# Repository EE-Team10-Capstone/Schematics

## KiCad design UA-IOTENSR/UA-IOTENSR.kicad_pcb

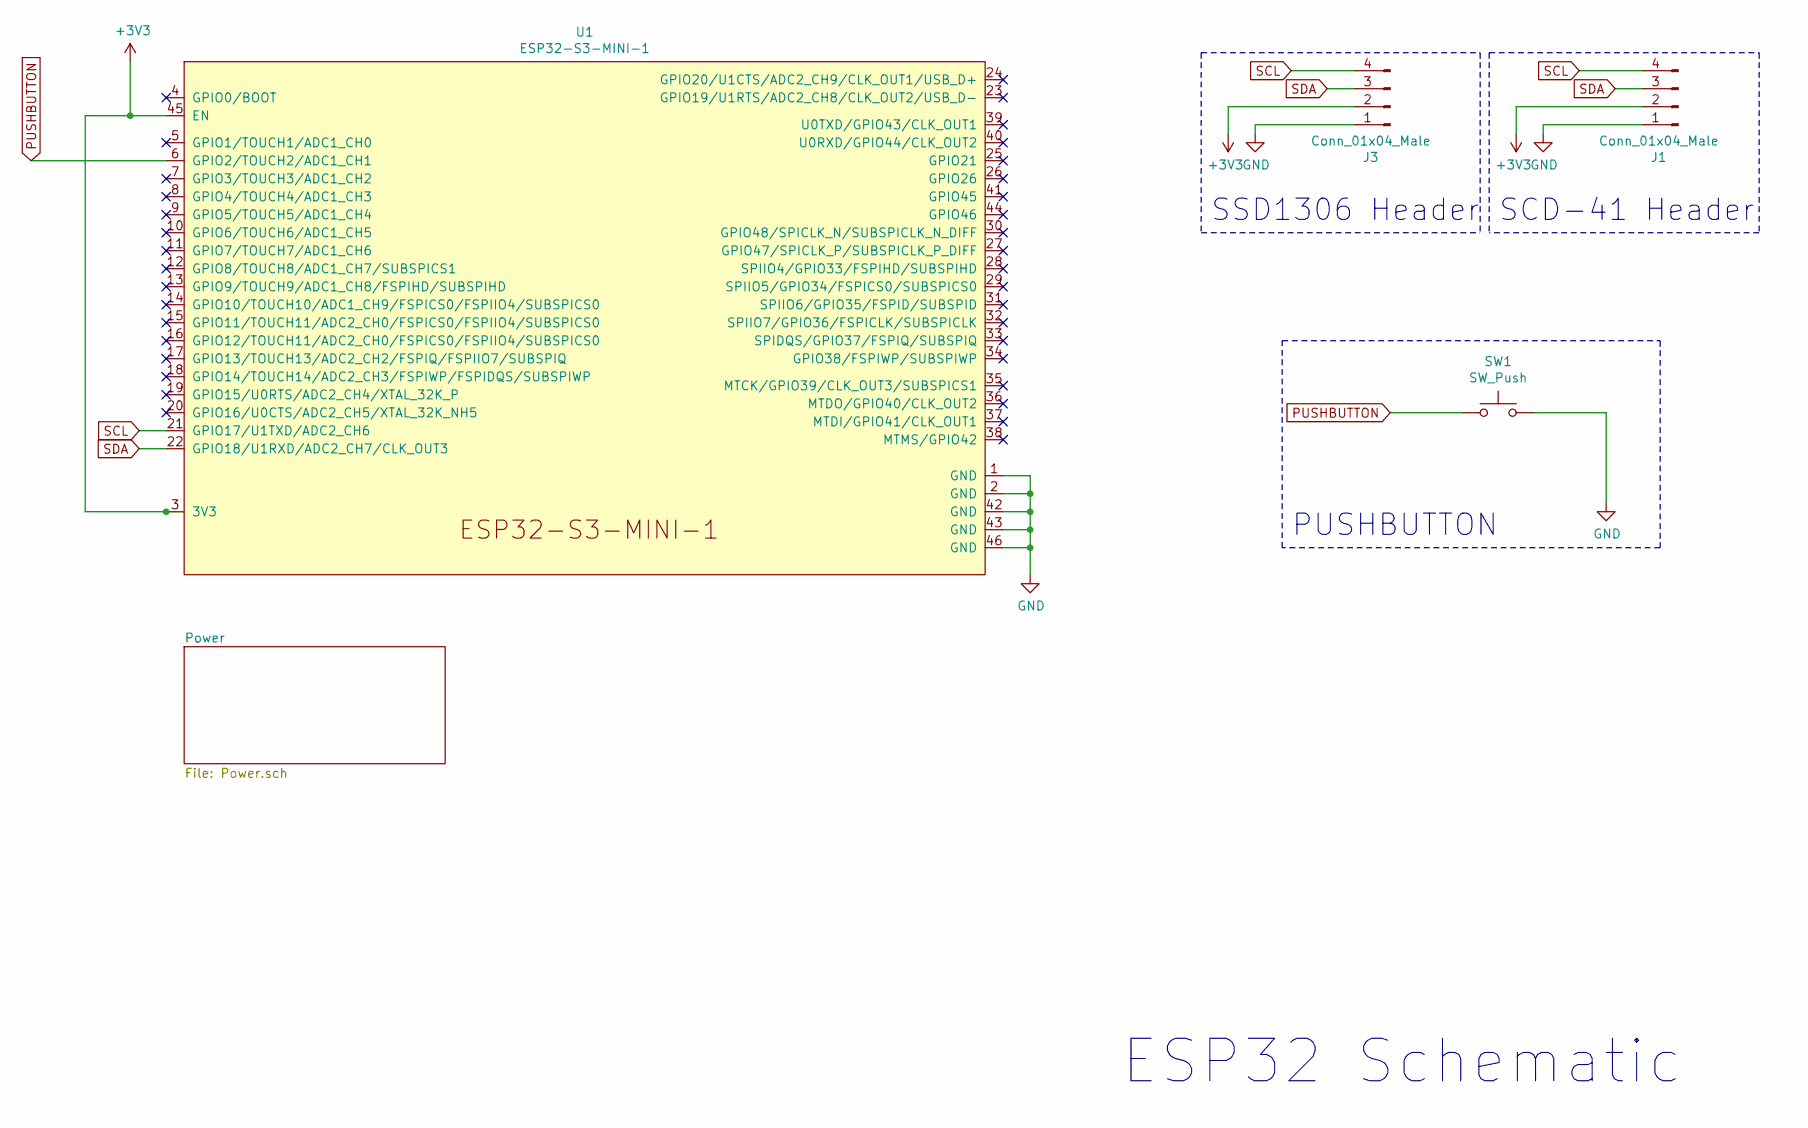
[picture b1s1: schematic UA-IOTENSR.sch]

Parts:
J1, J3: Conn_01x04_Male; PinSocket_1x04_P2.54mm_Vertical
SW1: SW_Push; SW_Tactile_SPST_Angled_PTS645Vx58-2LFS
U1: ESP32-S3-MINI-1; XCVR_ESP32-S3-MINI-1-N8

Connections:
BAT-: J1.1, J3.1, SW1.2, U1.1 (GND), U1.2 (GND), U1.42 (GND), U1.43 (GND), U1.46 (GND); also elsewhere on the board
PUSHBUTTON: SW1.1, U1.6 (GPIO2/TOUCH2/ADC1_CH1)
SCL: J1.4, J3.4, U1.21 (GPIO17/U1TXD/ADC2_CH6)
SDA: J1.3, J3.3, U1.22 (GPIO18/U1RXD/ADC2_CH7/CLK_OUT3)

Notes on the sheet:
ESP32 Schematic
SCD-41 Header
PUSHBUTTON
SSD1306 Header

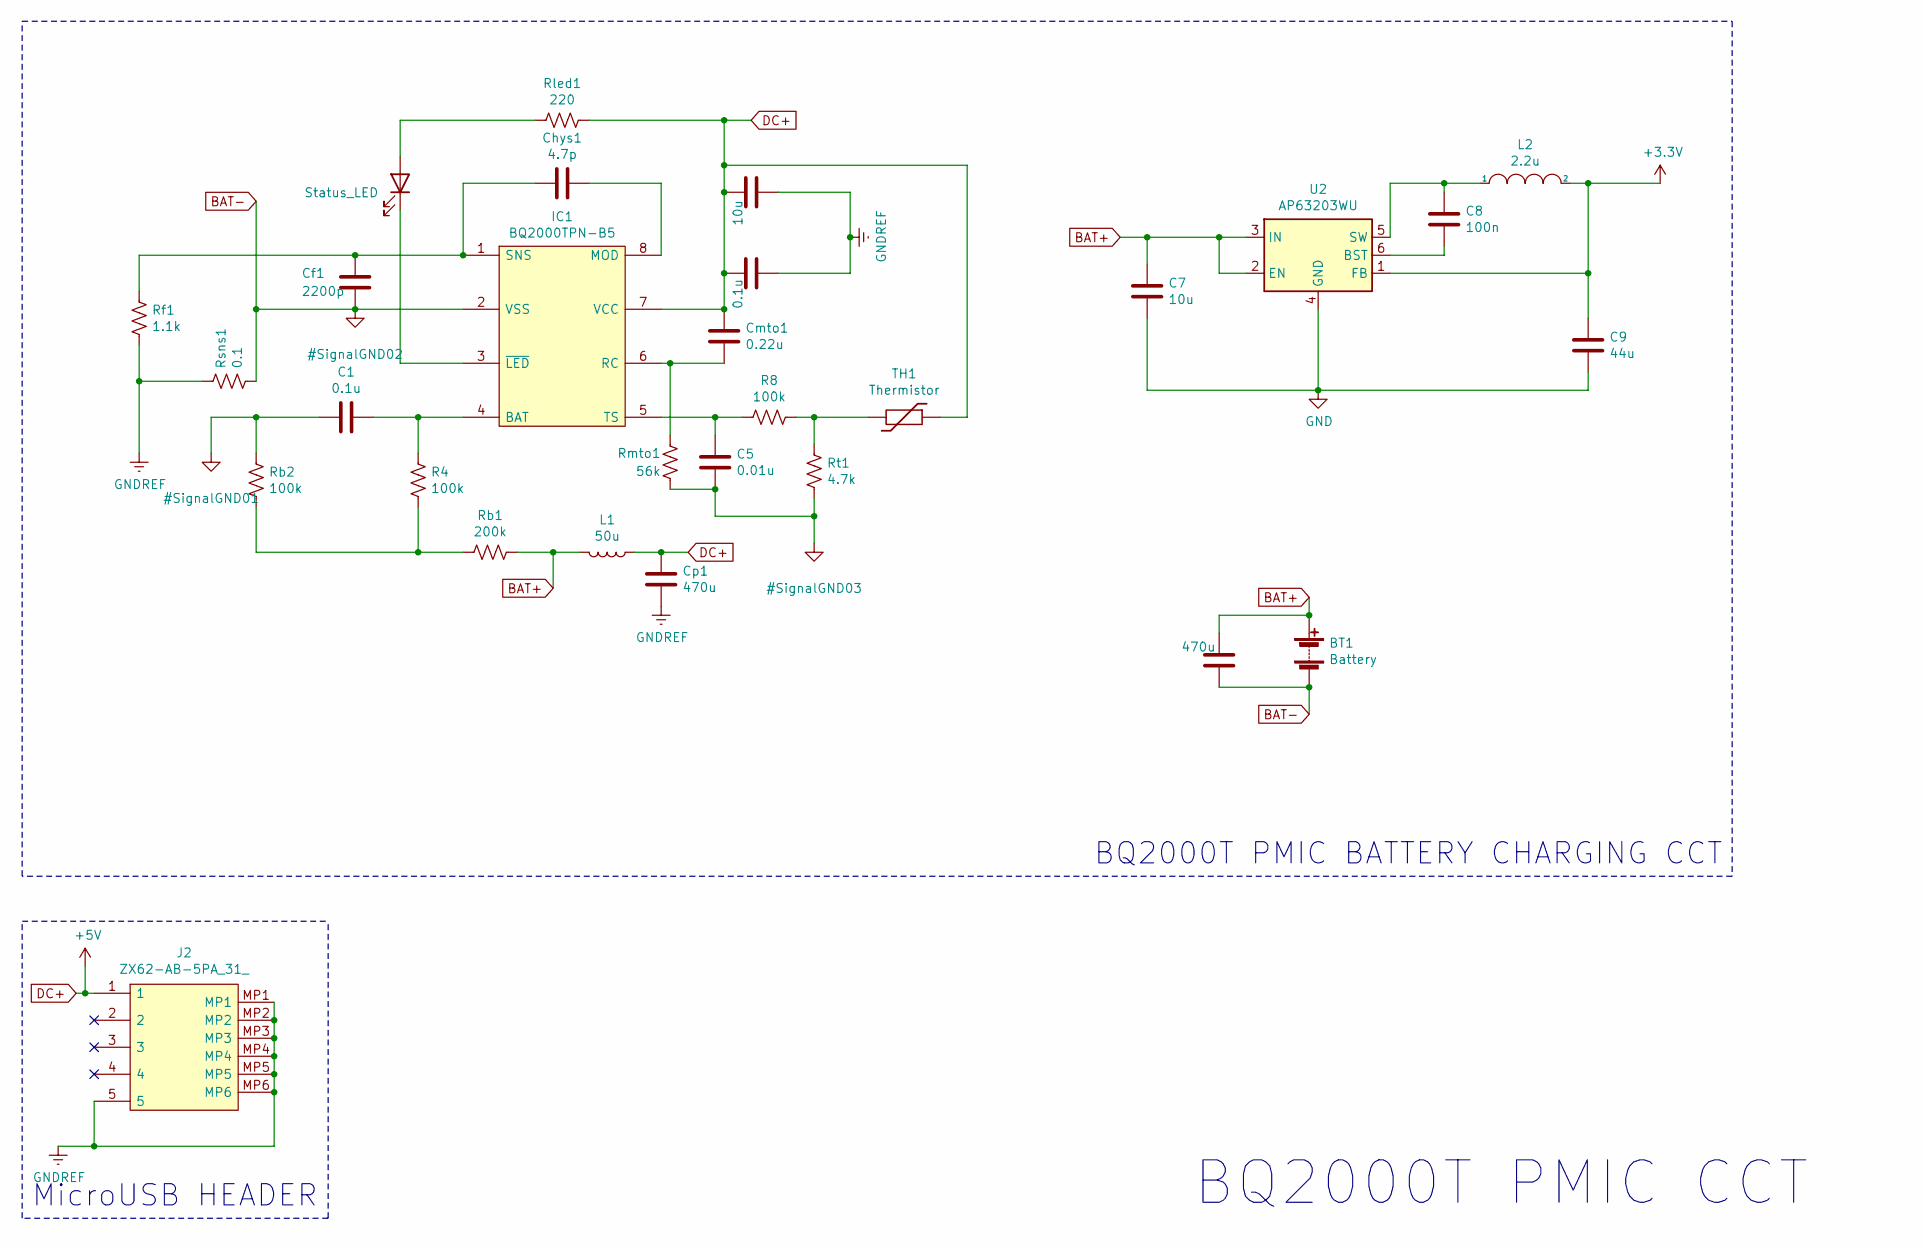
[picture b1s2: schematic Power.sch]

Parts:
BT1: Battery; BatteryHolder_TruPower_BH-331P_3xAA
Bypass_1: 10u; C_0805_2012Metric
Bypass_2: 0.1u; C_0805_2012Metric
Bypass_3: 470u; C_0805_2012Metric
C1: 0.1u; C_0805_2012Metric_Pad1.18x1.45mm_HandSolder
C5: 0.01u; C_0805_2012Metric
C7: 10u; C_0805_2012Metric_Pad1.18x1.45mm_HandSolder
C8: 100n; C_0805_2012Metric_Pad1.18x1.45mm_HandSolder
C9: 44u; C_0805_2012Metric_Pad1.18x1.45mm_HandSolder
Cf1: 2200p; C_0805_2012Metric
Chys1: 4.7p; C_0805_2012Metric
Cmto1: 0.22u; C_0805_2012Metric
Cp1: 470u; C_0805_2012Metric
D2: Status_LED; LED_1206_3216Metric
IC1: BQ2000TPN-B5; DIP794W53P254L959H508Q8N; Mouser Part Number 595-BQ2000TPN-B5
J2: ZX62-AB-5PA_31_; ZX62AB5PA31; Mouser Part Number 798-ZX62-AB-5PA31
L1: 50u; L_0805_2012Metric_Pad1.15x1.40mm_HandSolder
L2: 2.2u; L_0805_2012Metric_Pad1.15x1.40mm_HandSolder
R4, R8: 100k; RESC5025X70N
Rb1: 200k; RESC1608X55N
Rb2: 100k; RESC5025X70N
Rf1: 1.1k; ERA8A__0805_
Rled1: 220; RESC3116X65N
Rmto1: 56k; RESC2012X60N
Rsns1: 0.1; RESC6331X80N
Rt1: 4.7k; R_0805_2012Metric_Pad1.20x1.40mm_HandSolder
TH1: Thermistor; Thermistor_THT
U2: AP63203WU; TSOT-23-6

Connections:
BAT+: BT1.1 (+), Bypass_3.2, C7.1, L1.2, Rb1.1, U2.2 (EN), U2.3 (IN)
BAT-: BT1.2 (-), Bypass_3.1, C1.2, C5.2, C7.2, C9.2, Cf1.2, IC1.2 (VSS), Rb2.1, Rmto1.1, Rsns1.2, Rt1.2, U2.4 (GND); also elsewhere on the board
DC+: Bypass_1.2, Bypass_2.2, Cmto1.1, Cp1.1, IC1.7 (VCC), J2.1, L1.1, Rled1.1, TH1.1
GNDREF: Bypass_1.1, Bypass_2.1, Cp1.2, J2.5, J2.MP1, J2.MP2, J2.MP3, J2.MP4, J2.MP5, J2.MP6, Rf1.2, Rsns1.1
unnamed: C1.1, IC1.4 (BAT), R4.1
unnamed: C5.1, IC1.5 (TS), R8.2
unnamed: C8.1, L2.1, U2.5 (SW)
unnamed: C8.2, U2.6 (BST)
unnamed: Cf1.1, Chys1.2, IC1.1 (SNS), Rf1.1
unnamed: Chys1.1, IC1.8 (MOD)
unnamed: Cmto1.2, IC1.6 (RC), Rmto1.2
unnamed: D2.1 (K), IC1.3 (~LED)
unnamed: D2.2 (A), Rled1.2
unnamed: R4.2, Rb1.2, Rb2.2
unnamed: R8.1, Rt1.1, TH1.2

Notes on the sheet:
BQ2000T PMIC BATTERY CHARGING CCT
BQ2000T PMIC CCT
MicroUSB HEADER

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
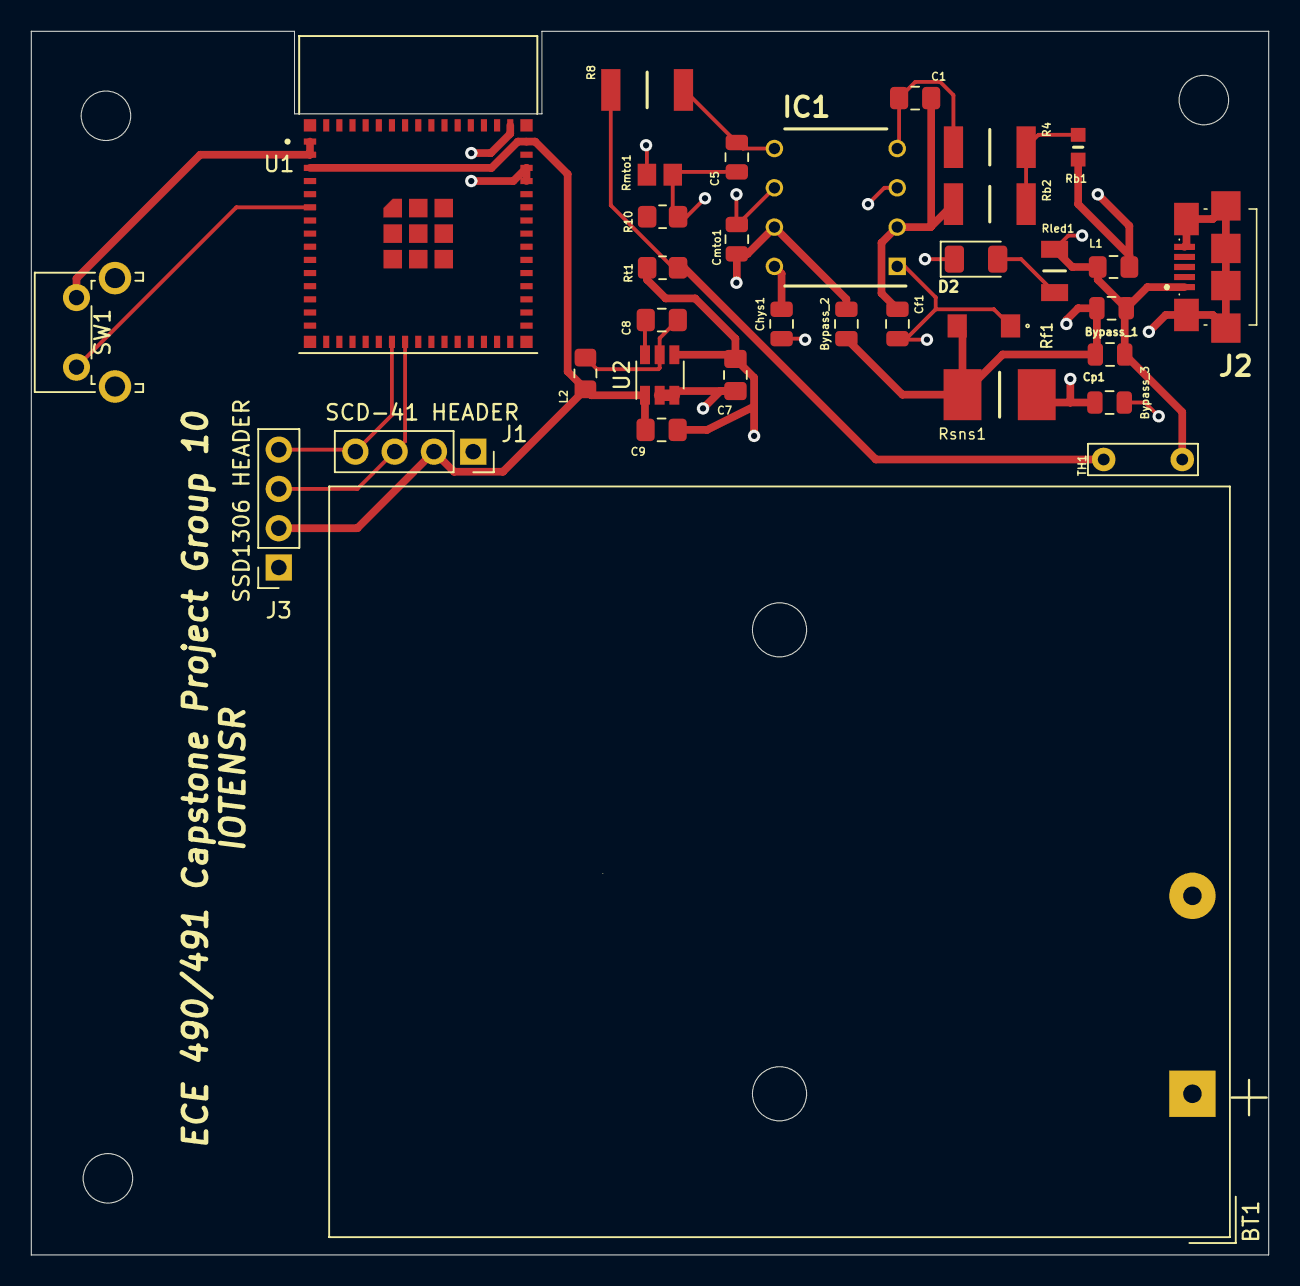
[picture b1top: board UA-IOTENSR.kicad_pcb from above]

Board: 4 copper layers, 80.0 x 79.1 mm, 34 parts (0 on the bottom side), 19 nets.

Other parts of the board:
R10: 5.7668k; R_0805_2012Metric_Pad1.20x1.40mm_HandSolder

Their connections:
BAT-: R10.2; also elsewhere on the board

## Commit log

2021-11-17 Adding libraries folder to the github
2021-11-17 Renaming Espressif KiCad Library Folder
2021-11-17 Creating SCD4X symbol and complete device schem
2021-11-17 Readjust folder and upload work done on schem 21/11/17
2021-11-20 Including the TI and Espressif libraries
2021-11-20 Removing rescue libraries
2021-11-21 Adding correct libraries and removing previous Power System design
2021-11-21 Libraries with more work done on Schem.
2021-11-23 Adding power system page, reorganizing libraries (more work needed)
2021-11-23 Adding peripherals page
2021-11-23 updated symbols; changed vdd to 3v3 global for pcb design later
2021-11-23 Finished LED bar graph array schem
2021-11-23 Made Peripheral sheet more pretty
2021-11-23 Organized PMIC schem
2021-11-23 Organized ESP32 main schem
2021-12-06 Reassessed components
    Removed bar graph led array and lm3914
2021-12-07 Adding the LED Schematic
2022-01-16 Reworking Power Schematic page for the change to NiMH tech
2022-01-16 Adding 5V power source to the Power.sch
2022-01-16 Adding missing values and line to the RC pin
2022-01-16 Adding labels to the JST connector and cleaning the original schematic
2022-01-18 Corrected some mistakes and cleaned up the new power schematic
2022-01-24 Updates to power schematic
    Updated LED Resistor Value
    Updated Page Title
2022-02-10 Add final missing values to power schematic
2022-02-11 Adding footprints; Updated to ESP32-S3-MINI
2022-02-12 All resistor and inductor footprints attached (except RTx)
2022-02-12 Assigned footprints to all symbols, removed unused parts
2022-02-12 Initial thermistor resistances included for temperature termination. MUST REDO TO LIMIT TEMPERATURE RANGE WHEN WE HAVE THE EQUIPMENT TO DO SO
2022-02-13 Fixing resistor values and overlapping resistors from previous commit
2022-02-14 Added 3V3 switch reg with footprint
2022-02-14 Completed regulator circuit; switched to 4-layer board setup
2022-02-14 Switched JST Conn to Battery Holder 3x AA
2022-02-16 Re-annotated schem, progress on layout
2022-03-04 Updated resistor values within the schematic
2022-03-11 Component labels and values updated
    Re labelled components to match the hand drawn schematic.
    Updated component values to reflect the redesign.
2022-03-22 Isolated GNDS and label updates
    Updated GND labels
2022-03-25 Placed james on silkscreen :sunglasses:
2022-04-04 Fixed GNDs and added new capacitors
    Adjusted ground connections, USB GND only connects to the Rf and the VCC by passing capacitors.
    Added by pass capactitors on VCC.
    Reconnected the thermistor in a pull high configuration
2022-04-06 removed dc+-, ground pour, M3 mounting holes
2022-04-07 pushbutton, esp antenna, condensing, title + james!!
2022-04-08 Zettai Ryouiki
